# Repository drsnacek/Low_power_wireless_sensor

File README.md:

# Low power wireless sensor
The intention is to build up a sensor powered by the batteries and wirelessly communicate with a server.

The first version is based on ESP8266 with the wifi connection to the server.
The DHT11 temprature/humidity sensor is powered through a NPN tranzistor that is controlled via the SW to unconnect the sensor power when the ESP is in the deep standby mode. MCP1700 is used to provide 3.3V for ESP, C2 is powering the ESP power peaks. TP4056 battery charger with the battery protection (BMS) built in is used togerther with Li-ion 18650 4.7V battery. R8 and R7 are a divider for measuring the battery state.

All components should provide very low power consumption in the deep standby mode to prolong the battery charnging needs as much as possible.

Component	Standby(µA)	Active(mA)

TP4056	50 µA (with LED: 2mA)	N/A
MCP1700	1,6 µA	250 mA (max)
ESP-12F	20-40 µA (deep sleep)	70-150 mA (Wi-Fi)
BMS	10 µA	N/A
Total energy consumption (standby)	~80-100 µA

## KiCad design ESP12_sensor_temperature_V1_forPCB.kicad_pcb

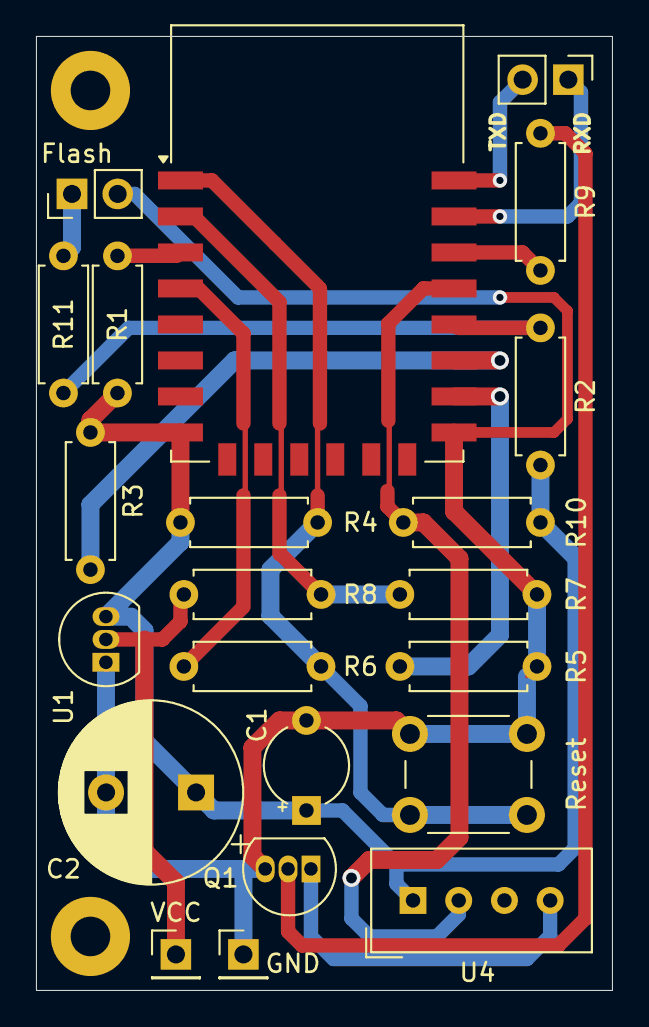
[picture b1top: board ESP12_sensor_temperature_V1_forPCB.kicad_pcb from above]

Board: 2 copper layers, 32.0 x 53.0 mm, 22 parts (0 on the bottom side), 17 nets.

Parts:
C1: 100n; CP_Radial_Tantal_D4.5mm_P5.00mm
C2: 1000uF; CP_Radial_D10.0mm_P5.00mm
Flash: Close for Flash; PinHeader_1x02_P2.54mm_Vertical
GND: GND; PinHeader_1x01_P2.54mm_Vertical
J6: TXD RXD; PinHeader_1x02_P2.54mm_Vertical
Q1: NPN C547C; TO-92L_Inline
R1, R9, R10: 10k; R_Axial_DIN0207_L6.3mm_D2.5mm_P7.62mm_Horizontal
R2, R3, R4: 4k7; R_Axial_DIN0207_L6.3mm_D2.5mm_P7.62mm_Horizontal
R5: 2k2; R_Axial_DIN0207_L6.3mm_D2.5mm_P7.62mm_Horizontal
R6: 150R; R_Axial_DIN0207_L6.3mm_D2.5mm_P7.62mm_Horizontal
R7: 68k; R_Axial_DIN0207_L6.3mm_D2.5mm_P7.62mm_Horizontal
R8: 220k; R_Axial_DIN0207_L6.3mm_D2.5mm_P7.62mm_Horizontal
R11: 120R; R_Axial_DIN0207_L6.3mm_D2.5mm_P7.62mm_Horizontal
Reset: Reset; SW_PUSH_6mm_H4.3mm
U1: MCP1700T-3302E TO; TO-92_Inline
U2: ESP-12E
U4: DHT11; Aosong_DHT11_5.5x12.0_P2.54mm
VCC: VCC; PinHeader_1x01_P2.54mm_Vertical

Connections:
GND: C1.2, C2.2, Flash.2, GND.1, Q1.3 (E), R5.2, R7.2, Reset.1, U1.1 (GND), U2.15 (GND)
unnamed: Flash.1, R11.2
unnamed: J6.1, U2.21 (GPIO3/RXD)
unnamed: J6.2, U2.22 (GPIO1/TXD)
unnamed: Q1.2 (B), R9.2
unnamed: Q1.1 (C), U4.4 (GND)
unnamed: C1.1, C2.1, R1.1, R2.1, R3.1, R4.1, R10.1, U1.3 (VO), U2.8 (VCC), U4.1 (VDD)
unnamed: R7.1, R8.2, U2.2 (ADC)
unnamed: R1.2, U2.3 (EN)
unnamed: R2.2, R11.1, U2.18 (GPIO0)
unnamed: R3.2, U2.17 (GPIO2)
unnamed: R10.2, U2.19 (GPIO4), U4.2 (DATA)
unnamed: R9.1, U2.20 (GPIO5)
unnamed: R5.1, U2.16 (GPIO15)
unnamed: R6.2, U2.4 (GPIO16)
unnamed: R4.2, R6.1, Reset.2, U2.1 (~RST)
VCC: R8.1, U1.2 (VI), VCC.1
